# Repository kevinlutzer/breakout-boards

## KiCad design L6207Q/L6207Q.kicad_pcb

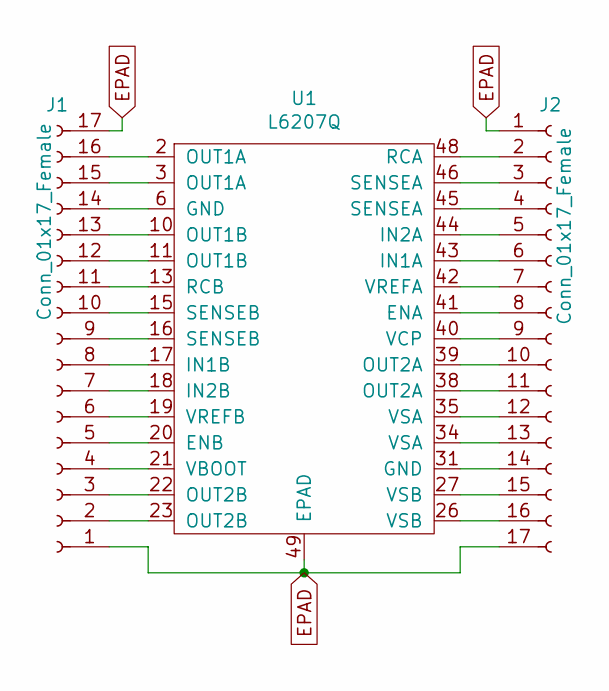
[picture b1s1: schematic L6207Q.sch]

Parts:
J1, J2: Conn_01x17_Female; PinHeader_1x17_P2.54mm_Vertical
U1: L6207Q; QFN50P700X700X60-49N

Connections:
EPAD: J1.1, J1.17, J2.1, J2.17, U1.49 (EPAD)
unnamed: J1.2, U1.23 (OUT2B)
unnamed: J1.3, U1.22 (OUT2B)
unnamed: J1.4, U1.21 (VBOOT)
unnamed: J1.5, U1.20 (ENB)
unnamed: J1.6, U1.19 (VREFB)
unnamed: J1.7, U1.18 (IN2B)
unnamed: J1.8, U1.17 (IN1B)
unnamed: J1.9, U1.16 (SENSEB)
unnamed: J1.10, U1.15 (SENSEB)
unnamed: J1.11, U1.13 (RCB)
unnamed: J1.12, U1.11 (OUT1B)
unnamed: J1.13, U1.10 (OUT1B)
unnamed: J1.14, U1.6 (GND)
unnamed: J1.15, U1.3 (OUT1A)
unnamed: J1.16, U1.2 (OUT1A)
unnamed: J2.2, U1.48 (RCA)
unnamed: J2.3, U1.46 (SENSEA)
unnamed: J2.4, U1.45 (SENSEA)
unnamed: J2.5, U1.44 (IN2A)
unnamed: J2.6, U1.43 (IN1A)
unnamed: J2.7, U1.42 (VREFA)
unnamed: J2.8, U1.41 (ENA)
unnamed: J2.9, U1.40 (VCP)
unnamed: J2.10, U1.39 (OUT2A)
unnamed: J2.11, U1.38 (OUT2A)
unnamed: J2.12, U1.35 (VSA)
unnamed: J2.13, U1.34 (VSA)
unnamed: J2.14, U1.31 (GND)
unnamed: J2.15, U1.27 (VSB)
unnamed: J2.16, U1.26 (VSB)

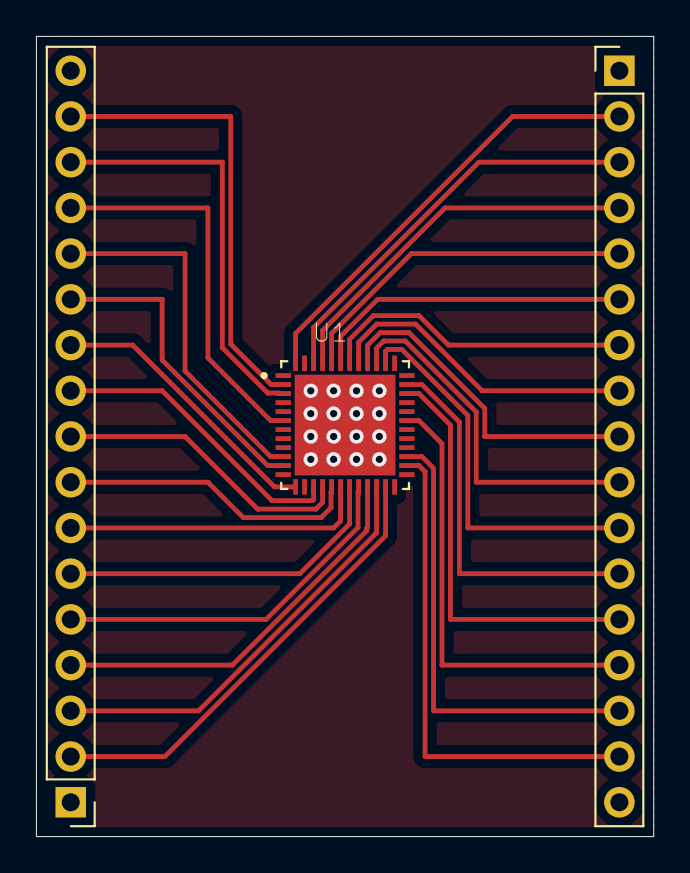
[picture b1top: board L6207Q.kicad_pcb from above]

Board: 2 copper layers, 34.3 x 44.5 mm, 3 parts (0 on the bottom side), 31 nets.

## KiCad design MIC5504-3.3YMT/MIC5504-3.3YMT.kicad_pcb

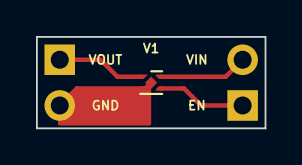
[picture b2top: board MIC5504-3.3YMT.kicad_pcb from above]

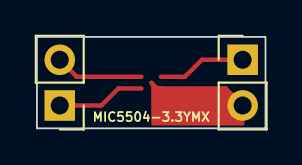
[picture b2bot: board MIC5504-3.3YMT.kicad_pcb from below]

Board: 2 copper layers, 12.7 x 5.1 mm, 3 parts (2 on the bottom side), 4 nets.

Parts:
J1, J2: Conn_01x02_Male; PinHeader_1x02_P2.54mm_Vertical
U1: MIC5504-3.3YMX; UDFN-4-1EP_1x1mm_P0.65mm_EP0.48x0.48mm

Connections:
EN: J2.1, U1.3 (EN)
GND: J1.2, U1.2 (GND), U1.5 (EP)
VIN: J2.2, U1.4 (VIN)
VOUT: J1.1, U1.1 (VOUT)

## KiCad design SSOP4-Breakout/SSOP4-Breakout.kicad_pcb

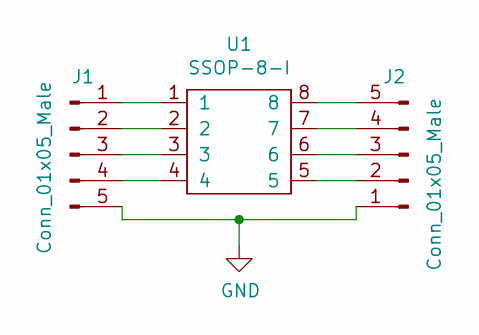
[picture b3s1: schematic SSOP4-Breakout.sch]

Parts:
J1, J2: Conn_01x05_Male; PinHeader_1x05_P2.54mm_Vertical
U1: SSOP-8-I; VSSOP-8_2.4x2.1mm_P0.5mm

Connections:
GND: J1.5, J2.1
unnamed: J1.1, U1.1
unnamed: J1.2, U1.2
unnamed: J1.3, U1.3
unnamed: J1.4, U1.4
unnamed: J2.2, U1.5
unnamed: J2.3, U1.6
unnamed: J2.4, U1.7
unnamed: J2.5, U1.8

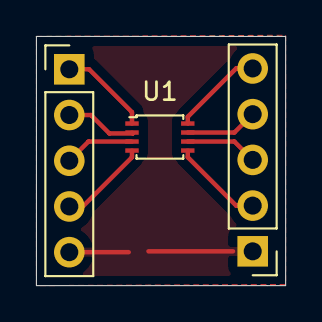
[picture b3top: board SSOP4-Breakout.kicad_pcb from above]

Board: 2 copper layers, 13.8 x 13.8 mm, 3 parts (0 on the bottom side), 9 nets.
